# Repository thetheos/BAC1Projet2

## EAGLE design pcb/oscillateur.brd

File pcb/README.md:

View this project on [CADLAB.io](https://cadlab.io/project/1678). 

# BAC1Projet2

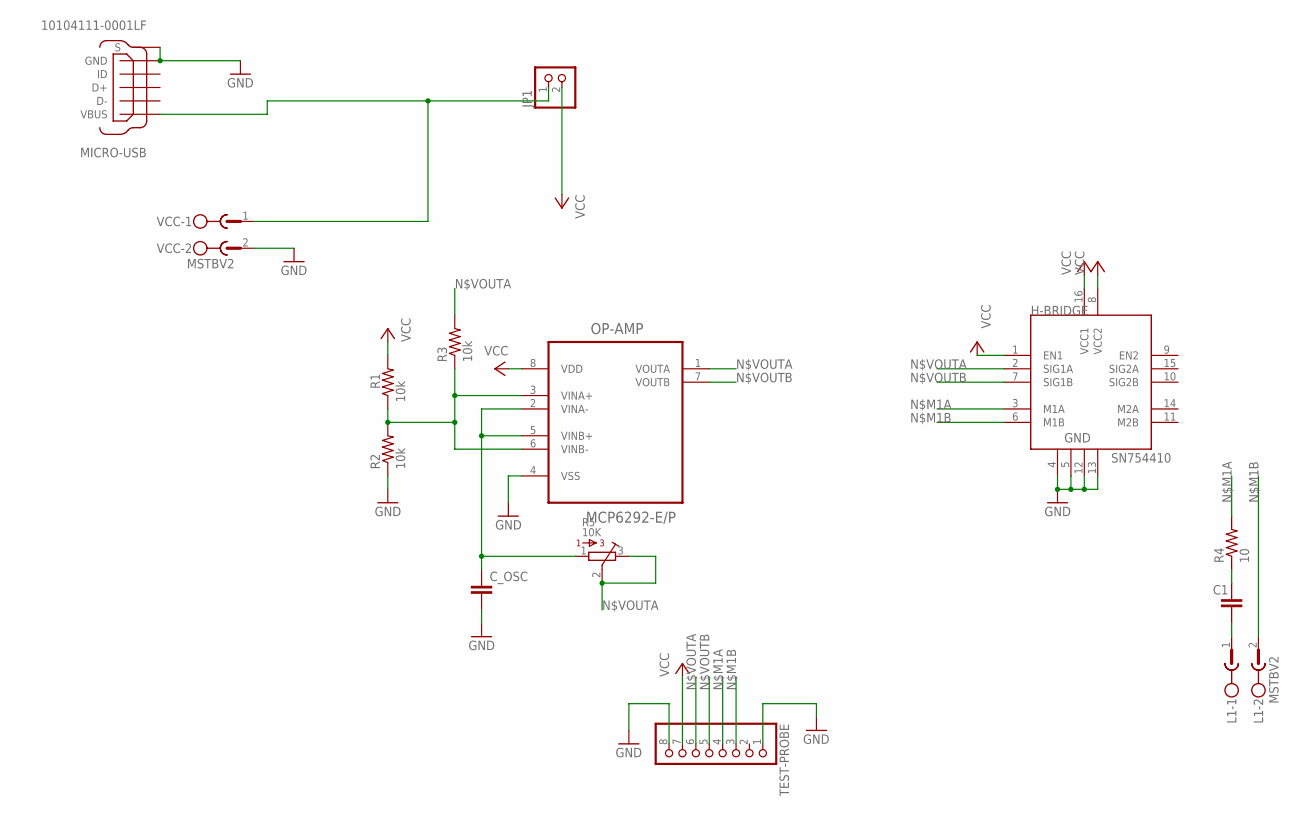
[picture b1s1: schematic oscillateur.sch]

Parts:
C1: C5/2.5; C5B2.5
C_OSC: C5/2.5; C5B2.5
H-BRIDGE: SN754410; DIP16
JP1: PINHD-1X2; 1X02
L1: MSTBV2
MICRO-USB: 10104111-0001LF; FRAMATOME_10104111-0001LF
OP-AMP: MCP6292-E/P; DIP254P762X432-8
R1, R2, R3: 10k; 0207/10
R4: 10; 0207/10
R5: 10K; 3362R
TEST-PROBE: PINHD-1X8; 1X08
VCC: MSTBV2

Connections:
GND: C_OSC.2, H-BRIDGE.4, H-BRIDGE.5, H-BRIDGE.12, H-BRIDGE.13, MICRO-USB.5 (GND), MICRO-USB.6 (S), MICRO-USB.7 (S), MICRO-USB.8 (S), MICRO-USB.9 (S), OP-AMP.4 (VSS), R2.1, TEST-PROBE.1, TEST-PROBE.8, VCC.2
unnamed: OP-AMP.3 (VINA+), OP-AMP.6 (VINB-), R1.1, R2.2, R3.1
unnamed: JP1.1, MICRO-USB.1 (VBUS), VCC.1
unnamed: C1.1, R4.1
unnamed: C_OSC.1, OP-AMP.2 (VINA-), OP-AMP.5 (VINB+), R5.1
unnamed: C1.2, L1.1
N$M1A: H-BRIDGE.3 (M1A), R4.2, TEST-PROBE.4
N$M1B: H-BRIDGE.6 (M1B), L1.2, TEST-PROBE.3
N$VOUTA: H-BRIDGE.2 (SIG1A), OP-AMP.1 (VOUTA), R3.2, R5.2, R5.3, TEST-PROBE.6
N$VOUTB: H-BRIDGE.7 (SIG1B), OP-AMP.7 (VOUTB), TEST-PROBE.5
VCC: H-BRIDGE.1 (EN1), H-BRIDGE.8 (VCC2), H-BRIDGE.16 (VCC1), JP1.2, OP-AMP.8 (VDD), R1.2, TEST-PROBE.7

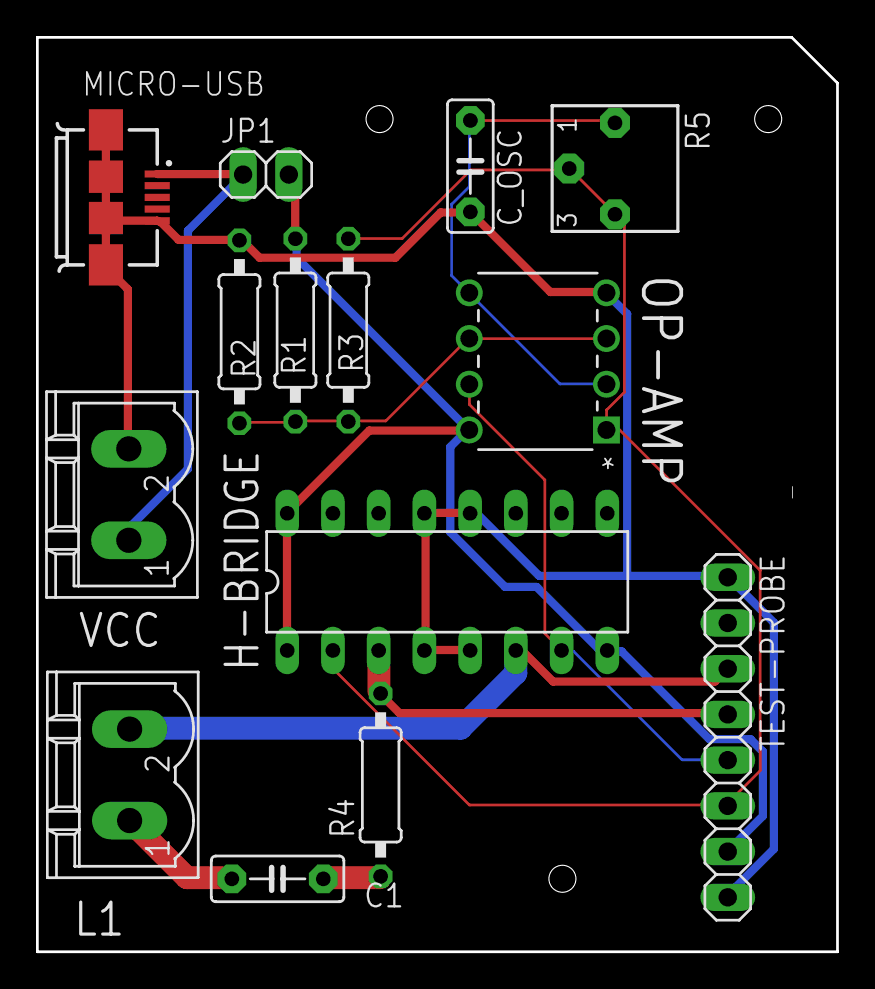
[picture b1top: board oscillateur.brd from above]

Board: 2 copper layers, 44.5 x 50.8 mm, 14 parts (0 on the bottom side), 11 nets.

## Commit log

2019-04-07 Backlink to CADLAB.io has been added.
2019-05-04 add all
2020-02-15 Set theme jekyll-theme-cayman
